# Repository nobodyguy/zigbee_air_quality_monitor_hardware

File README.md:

# Zigbee air quality monitor board
Opensource HA compatible air quality monitor with CO2, temperature and humidity measurements.

* KiCAD 8.X required 
* Includes nrf52840 module
* Includes SCD40/SCD41 module

## Firmware
https://github.com/nobodyguy/zigbee_air_quality_monitor_firmware

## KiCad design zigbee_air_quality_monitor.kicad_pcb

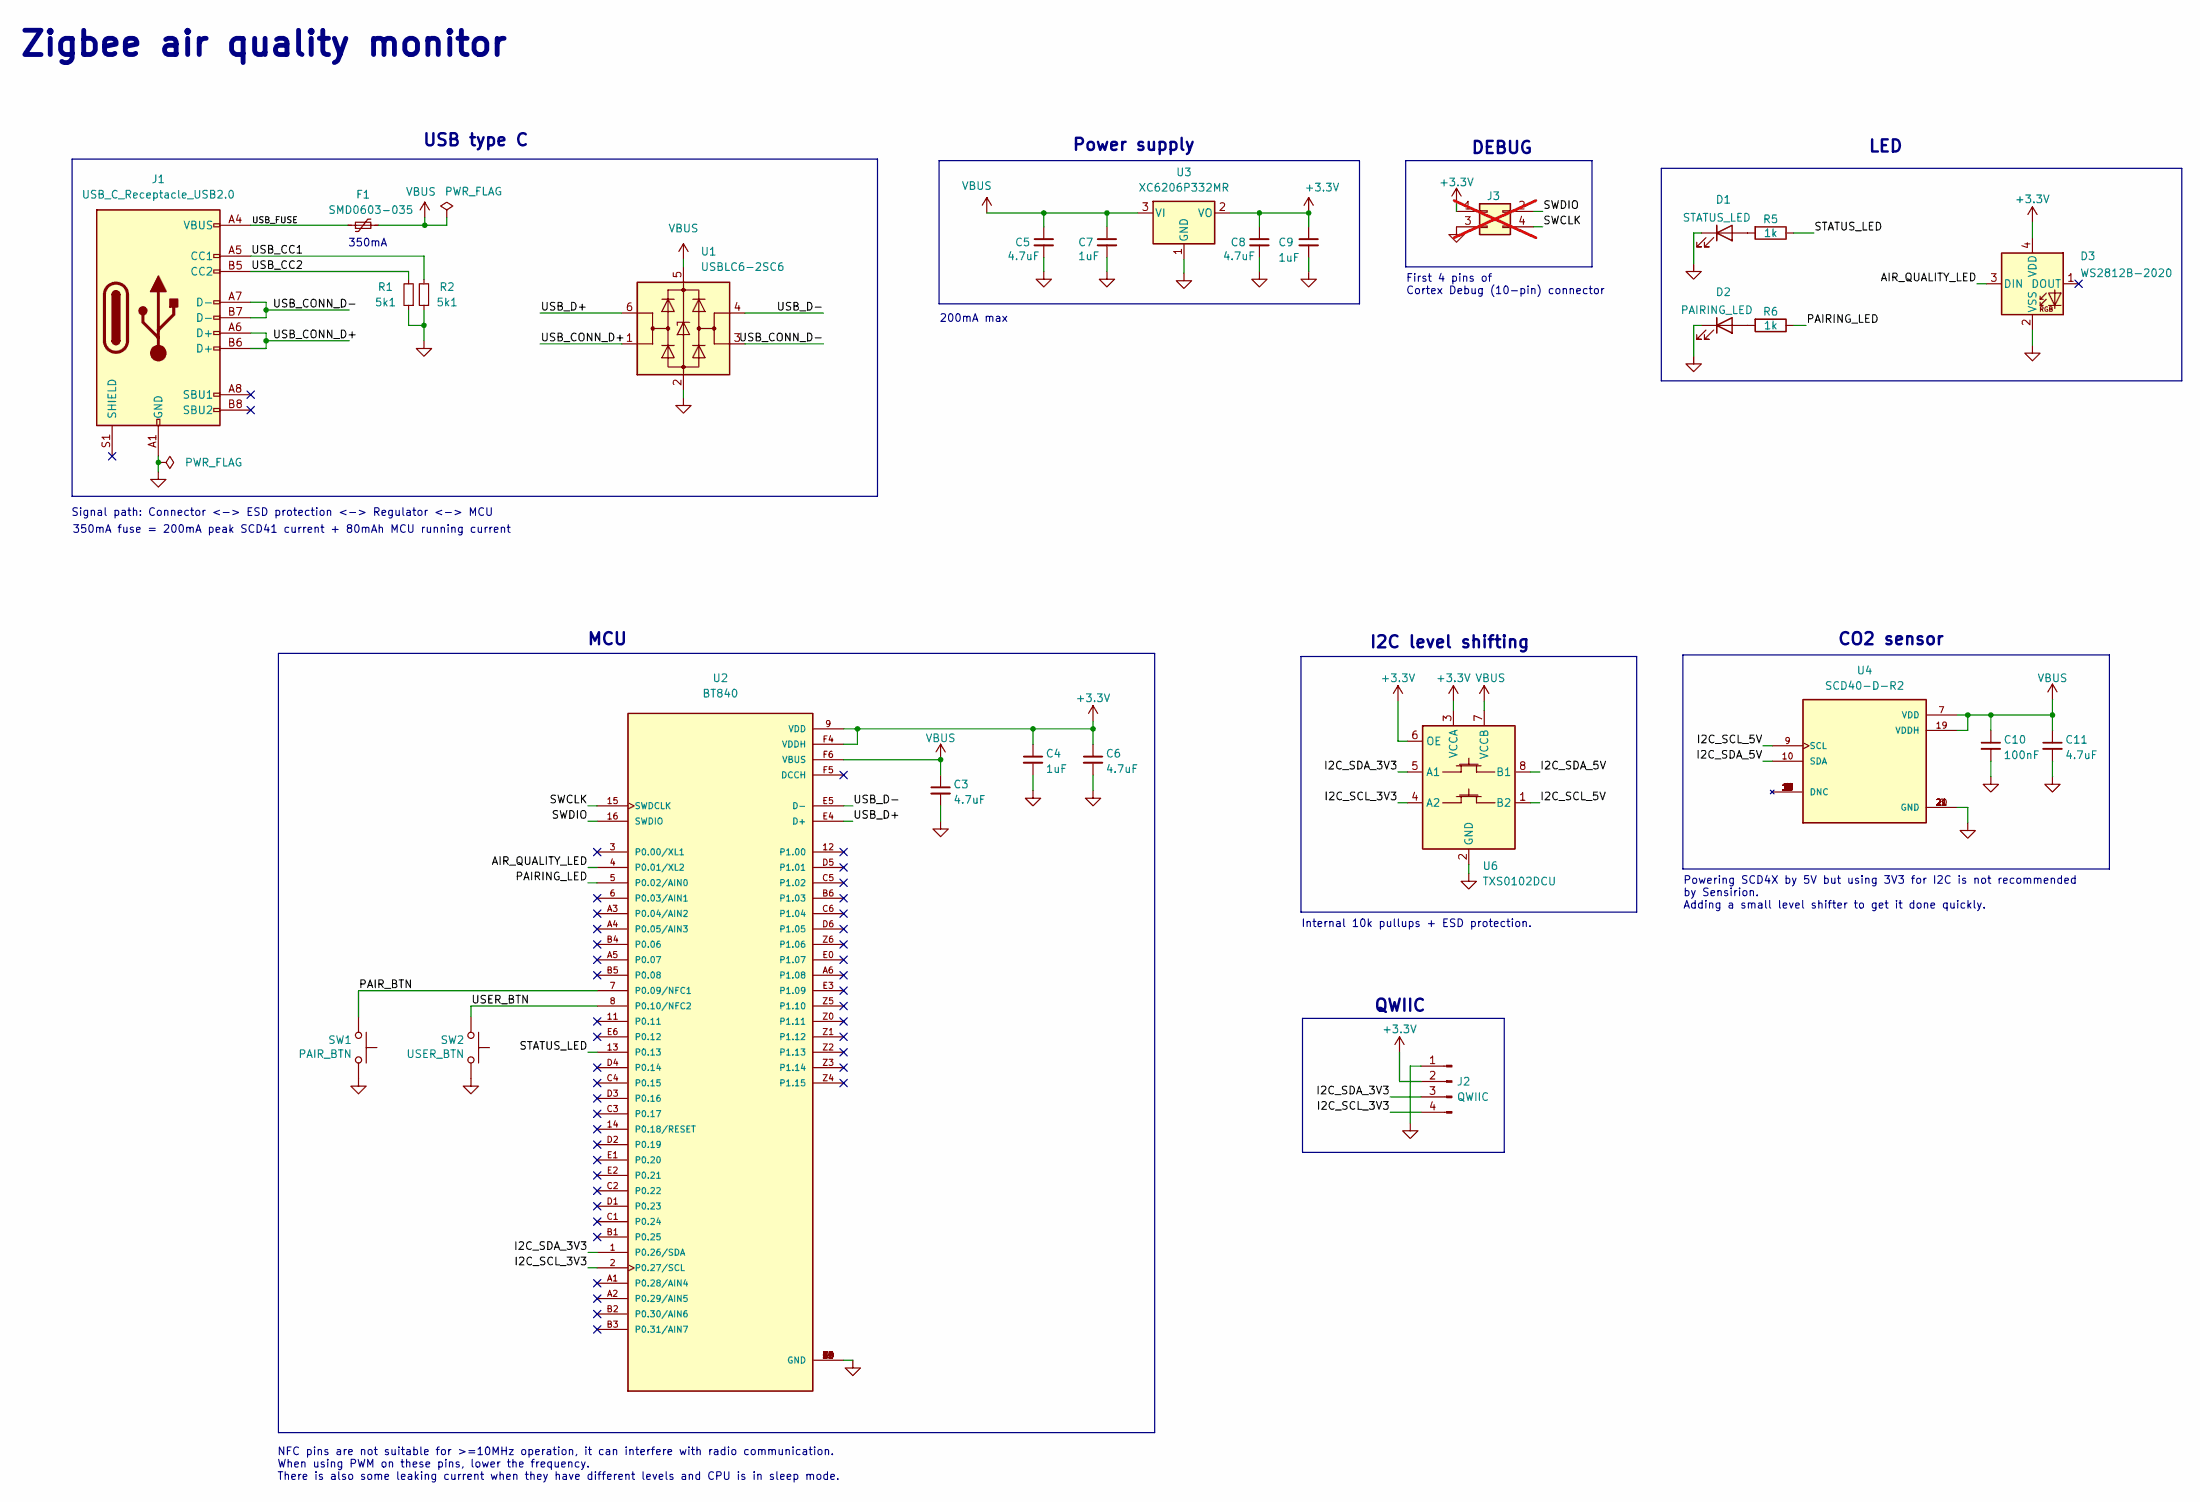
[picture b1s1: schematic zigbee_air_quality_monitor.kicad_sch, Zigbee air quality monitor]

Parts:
C3, C5, C6, C8, C11: 4.7uF; C_0603_1608Metric; LCSC Part C19666
C4, C7, C9: 1uF; C_0603_1608Metric; LCSC Part C15849
C10: 100nF; C_0603_1608Metric; LCSC Part C14663
D1: STATUS_LED; LED_0603_1608Metric; LCSC Part C965804
D2: PAIRING_LED; LED_0603_1608Metric; LCSC Part C965807
D3: WS2812B-2020; LED_WS2812B_PLCC4_5.0x5.0mm_P3.2mm; LCSC Part C965555
F1: SMD0603-035; Fuse_0603_1608Metric; LCSC Part C910818
J1: USB_C_Receptacle_USB2.0; USB_C_Receptacle_HRO_TYPE-C-31-M-12; LCSC Part C165948
J2: QWIIC; JST_SH_SM04B-SRSS-TB_1x04-1MP_P1.00mm_Horizontal; LCSC Part C9900058894
J3: Conn_02x02_Odd_Even; PinHeader_2x02_P1.27mm_Vertical; not fitted
R1, R2: 5k1; R_0603_1608Metric; LCSC Part C23186
R5, R6: 1k; R_0603_1608Metric; LCSC Part C21190
SW1: PAIR_BTN; SW_Push_SPST_NO_Alps_SKRK; LCSC Part C115357
SW2: USER_BTN; SW_Push_SPST_NO_Alps_SKRK; LCSC Part C115357
U1: USBLC6-2SC6; SOT-23-6; LCSC Part C2827654
U2: BT840; LCSC Part C5182373
U3: XC6206P332MR; SOT-23; LCSC Part C5446
U4: SCD40-D-R2; XDCR_SCD41-D-R2; PARTREV 1.2; LCSC Part C3659421
U6: TXS0102DCU; VSSOP-8_2.3x2mm_P0.5mm; LCSC Part C53434

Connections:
+3.3V: C4.1, C6.1, C8.1, C9.1, D3.4 (VDD), J2.2, J3.1, U2.9 (VDD), U2.F4 (VDDH), U3.2 (VO), U6.3 (VCCA), U6.6 (OE)
/AIR_QUALITY_LED: D3.3 (DIN), U2.4 (P0.01/XL2)
/I2C_SCL_3V3: J2.4, U2.2 (P0.27/SCL), U6.4 (A2)
/I2C_SCL_5V: U4.9 (SCL), U6.1 (B2)
/I2C_SDA_3V3: J2.3, U2.1 (P0.26/SDA), U6.5 (A1)
/I2C_SDA_5V: U4.10 (SDA), U6.8 (B1)
/PAIRING_LED: R6.1, U2.5 (P0.02/AIN0)
/PAIR_BTN: SW1.1, U2.7 (P0.09/NFC1)
/STATUS_LED: R5.1, U2.13 (P0.13)
/SWCLK: J3.4, U2.15 (SWDCLK)
/SWDIO: J3.2, U2.16 (SWDIO)
/USB_CC1: J1.A5 (CC1), R2.2
/USB_CC2: J1.B5 (CC2), R1.2
/USB_CONN_D+: J1.A6 (D+), J1.B6 (D+), U1.1 (I/O1)
/USB_CONN_D-: J1.A7 (D-), J1.B7 (D-), U1.3 (I/O2)
/USB_D+: U1.6 (I/O1), U2.E4 (D+)
/USB_D-: U1.4 (I/O2), U2.E5 (D-)
/USB_FUSE: F1.1, J1.A4 (VBUS), J1.A9 (VBUS), J1.B4 (VBUS), J1.B9 (VBUS)
/USER_BTN: SW2.1, U2.8 (P0.10/NFC2)
GND: C3.2, C4.2, C5.2, C6.2, C7.2, C8.2, C9.2, C10.2, C11.2, D1.1 (K), D2.1 (K), D3.2 (VSS), J1.A1 (GND), J1.A12 (GND), J1.B1 (GND), J1.B12 (GND), J2.1, J3.3, R1.1, R2.1, SW1.2, SW2.2, U1.2 (GND), U2.10 (GND), U2.A0 (GND), U2.B0 (GND), U2.C0 (GND), U2.D0 (GND), U2.F0 (GND), U2.F1 (GND), U2.F2 (GND), U2.F3 (GND), U3.1 (GND), U4.6 (GND), U4.20 (GND), U4.21 (GND), U6.2 (GND)
unnamed: D1.2 (A), R5.2
unnamed: D2.2 (A), R6.2
VBUS: C3.1, C5.1, C7.1, C10.1, C11.1, F1.2, U1.5 (VBUS), U2.F6 (VBUS), U3.3 (VI), U4.7 (VDD), U4.19 (VDDH), U6.7 (VCCB)

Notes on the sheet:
Internal 10k pullups + ESD protection.
DEBUG
LED
MCU
350mA
Power supply
200mA max
NFC pins are not suitable for >=10MHz operation, it can interfere with radio communication. When using PWM on these pins, lower the frequency. There is also some leaking current when they have different levels and CPU is in sleep mode.
Powering SCD4X by 5V but using 3V3 for I2C is not recommended by Sensirion. Adding a small level shifter to get it done quickly.
USB type C
CO2 sensor
First 4 pins of Cortex Debug (10-pin) connector
Signal path: Connector <-> ESD protection <-> Regulator <-> MCU
I2C level shifting
350mA fuse = 200mA peak SCD41 current + 80mAh MCU running current
Zigbee air quality monitor
QWIIC

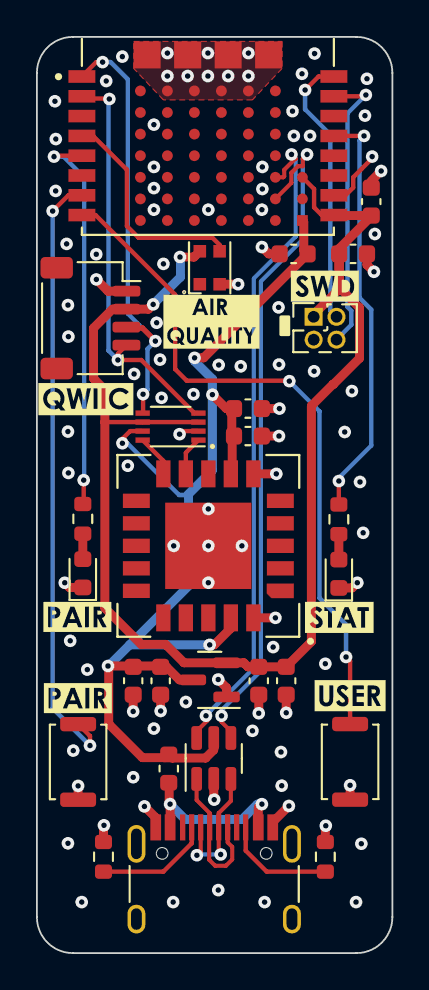
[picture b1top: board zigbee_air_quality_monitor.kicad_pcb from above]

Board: 4 copper layers, 19.8 x 50.9 mm, 35 parts (1 on the bottom side), 23 nets.

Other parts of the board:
G1: LOGO
kibuzzard-63D9ACF8: G***; kibuzzard-63D9ACF8
kibuzzard-63D64B8B, kibuzzard-63D64B8B#2: G***; kibuzzard-63D64B8B
kibuzzard-63D64B66: G***; kibuzzard-63D64B66
kibuzzard-63D6450F: G***; kibuzzard-63D6450F
kibuzzard-63D64107: G***; kibuzzard-63D64107
kibuzzard-63D64589: G***; footprint

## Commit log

2023-01-20 Zigbee module, PN and jtag schematics
2023-01-29 Finished schematics, added 3D models
2023-02-04 Rough part placement
2024-02-25 Routing WIP
2024-02-25 Added CI
2024-02-25 KiBot config 3D settings
2024-02-25 CI test
2024-02-26 Simplified CI
2024-02-26 USB routing WIP
2024-02-26 More CI output tweaks
2024-02-26 All parts routed
2024-02-26 CI diffing fix
2024-02-27 Added 300mA LDO
2024-02-27 Added level translator for SCD40
2024-02-28 Added round corners to PCB
2024-02-28 Added inner GND planes, backside silkscreen label
2024-02-28 Routing done, via stitching done
2024-02-28 Fixed silkscreen logo designator to make KiBot happy
2024-02-29 Fixed QWIIC connector footprint and model
2024-03-01 Added PCB render animation
2024-03-02 Changed supply voltage for WS2812-2020 LED to 5V
2024-03-02 LED exact name, SCD40 exact name
2024-03-02 Fixed clipped silkscreen, ERC+DRC warnings
2024-03-02 Fixed SCD footprint name
2024-03-08 Symbol and footprint project libs cleanup
2024-08-01 Cost optimizations
2024-08-01 rev2
    Fixed RGB LED footprint, removed problematic button caps, cleaning
2024-08-01 Manufacturing fixes
2024-08-31 Docs update
2024-08-31 Added enclosure
2024-09-01 Buttons aligned
